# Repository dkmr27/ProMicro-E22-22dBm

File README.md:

# ProMicro-E22-22dBm
A PCB for nRF52840 promicro using Ebyte E22-xxxM22S 22dBm modules

As with a lot of my boards, the extra components are optional. Reset button and 2x 1M ohm 1206 (R1/R2) resistors recomended at minimum.
A hardware low voltage reset IC was included in the design but never tested.

Compatible modules are:
* E22-170M22S SX1262 150MHz to 170MHz (works great at 173MHz)
* E22-400M22S SX1268 410MHz to 493MHz
* E22-900M22S SX1262 850MHz to 930MHz (works with MeshCore faketec firmware)

The production folder contains a .zip file suitable for PCB production (JLCPCB etc.)

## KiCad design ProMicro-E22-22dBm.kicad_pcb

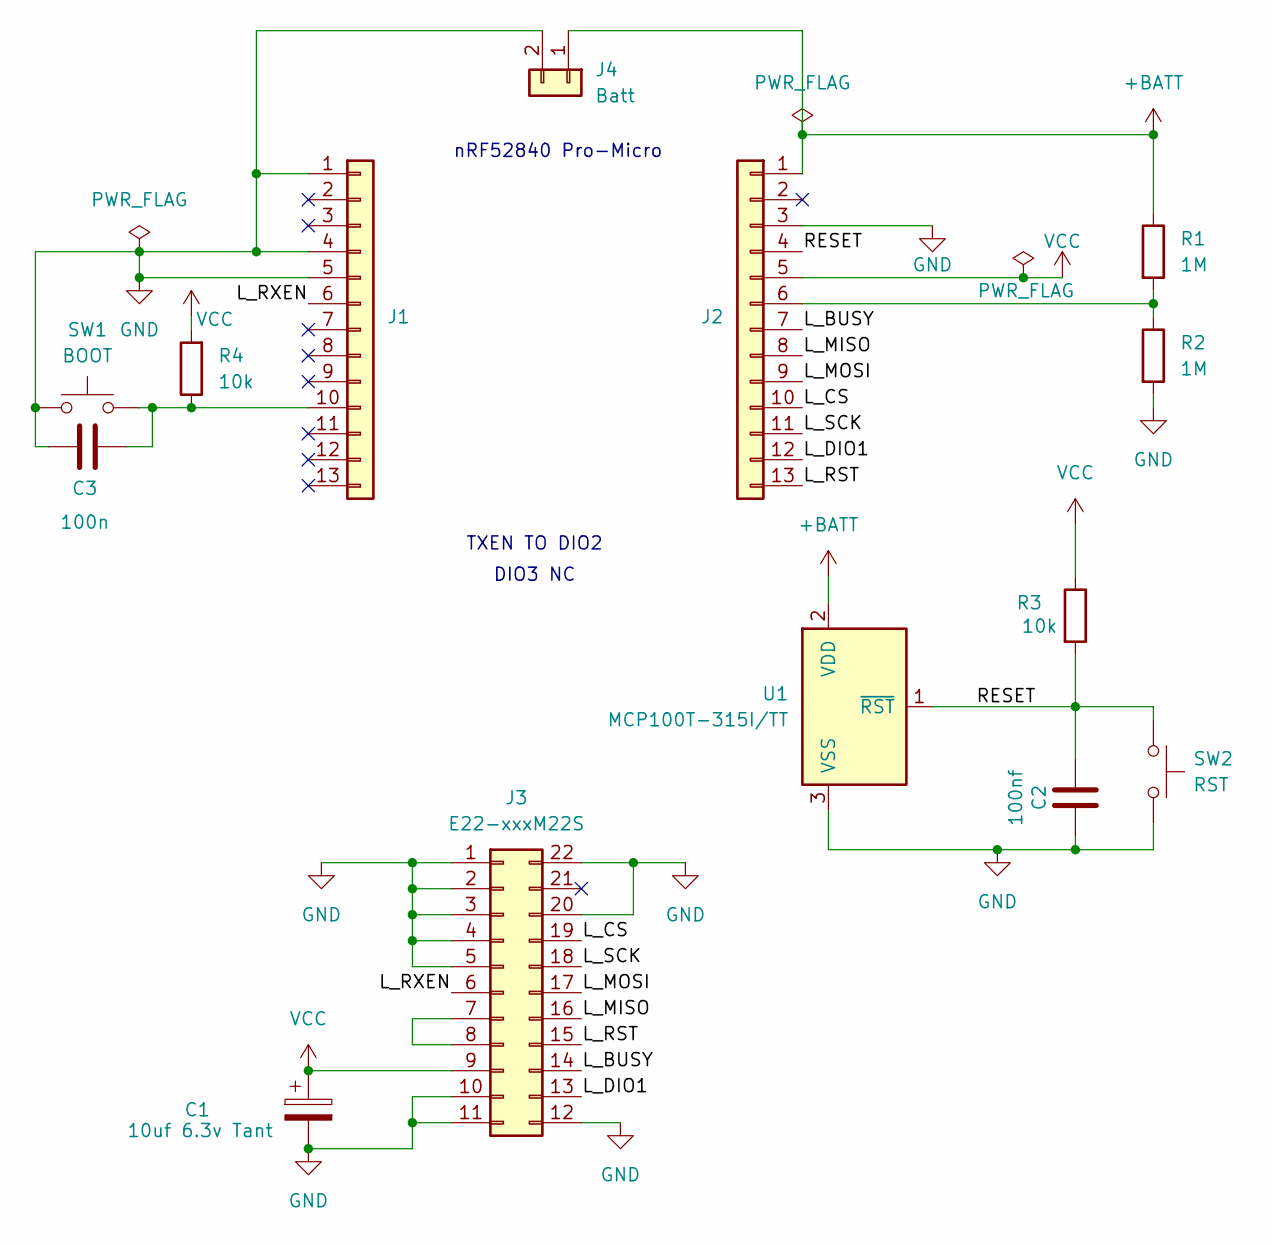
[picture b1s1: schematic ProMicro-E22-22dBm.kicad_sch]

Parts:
C1: 10uf 6.3v Tant; CP_EIA-3216-18_Kemet-A_HandSolder
C2: 100nf; C_1206_3216Metric_Pad1.33x1.80mm_HandSolder
C3: 100n; C_1206_3216Metric_Pad1.33x1.80mm_HandSolder
J1, J2: PinSocket_1x13_P2.54mm_Vertical
J3: E22-xxxM22S; PE22(900M22S)
J4: Batt; SolderWire-0.75sqmm_1x02_P4.8mm_D1.25mm_OD2.3mm
R1, R2: 1M; R_1206_3216Metric
R3, R4: 10k; R_1206_3216Metric
SW1: BOOT; SW_SPST_TS-1088-xR020
SW2: RST; SW_SPST_TS-1088-xR020
U1: MCP100T-315I/TT; SOT-23_Handsoldering

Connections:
+BATT: J2.1, J4.1, R1.1, U1.2 (VDD)
/L_BUSY: J2.7, J3.14
/L_CS: J2.10, J3.19
/L_DIO1: J2.12, J3.13
/L_MISO: J2.8, J3.16
/L_MOSI: J2.9, J3.17
/L_RST: J2.13, J3.15
/L_RXEN: J1.6, J3.6
/L_SCK: J2.11, J3.18
/RESET: C2.1, J2.4, R3.2, SW2.1, U1.1 (~RST)
GND: C1.2, C2.2, C3.1, J1.1, J1.4, J1.5, J2.3, J3.1, J3.2, J3.3, J3.4, J3.5, J3.10, J3.11, J3.12, J3.20, J3.22, J4.2, R2.2, SW1.1, SW2.2, U1.3 (VSS)
unnamed: C3.2, J1.10, R4.1, SW1.2
unnamed: J2.6, R1.2, R2.1
unnamed: J3.7, J3.8
VCC: C1.1, J2.5, J3.9, R3.1, R4.2

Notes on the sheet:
nRF52840 Pro-Micro
DIO3 NC
TXEN TO DIO2

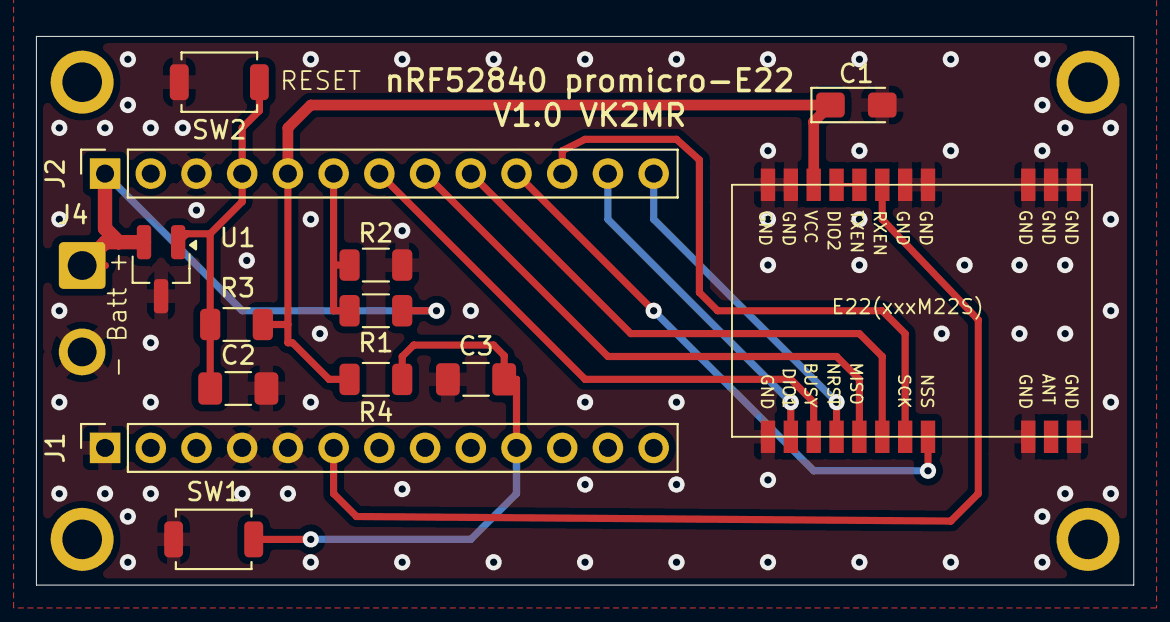
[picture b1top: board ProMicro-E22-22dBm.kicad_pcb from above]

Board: 2 copper layers, 61.0 x 30.5 mm, 14 parts (0 on the bottom side), 15 nets.
